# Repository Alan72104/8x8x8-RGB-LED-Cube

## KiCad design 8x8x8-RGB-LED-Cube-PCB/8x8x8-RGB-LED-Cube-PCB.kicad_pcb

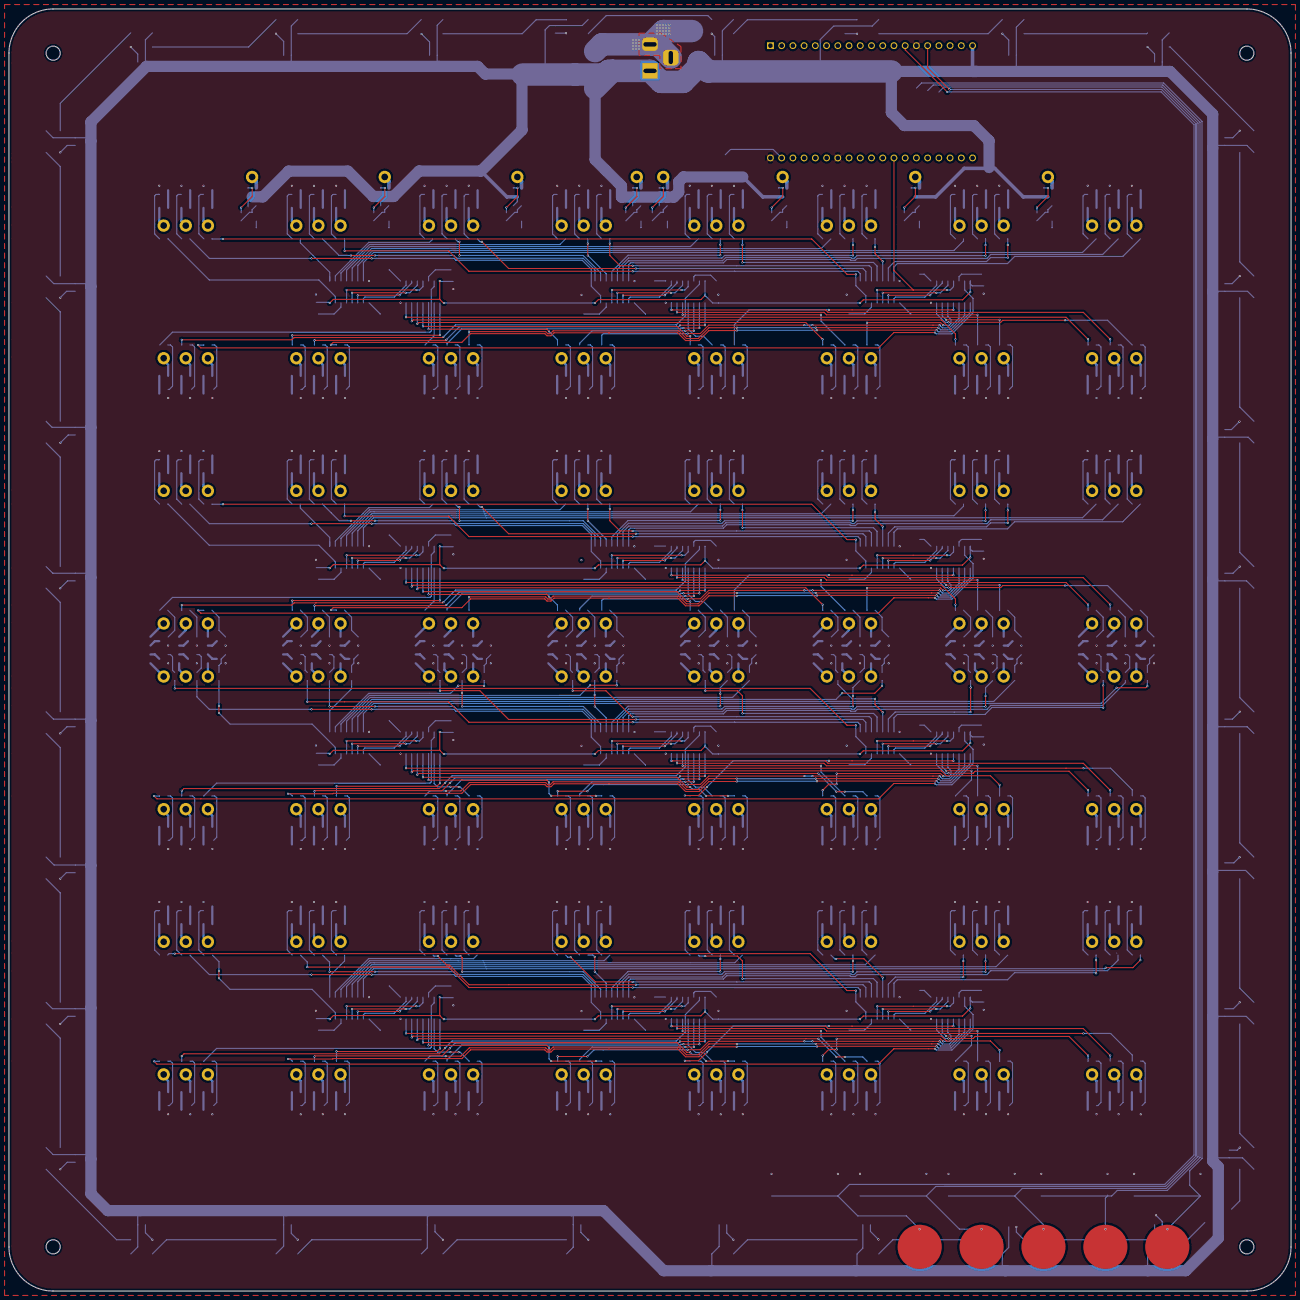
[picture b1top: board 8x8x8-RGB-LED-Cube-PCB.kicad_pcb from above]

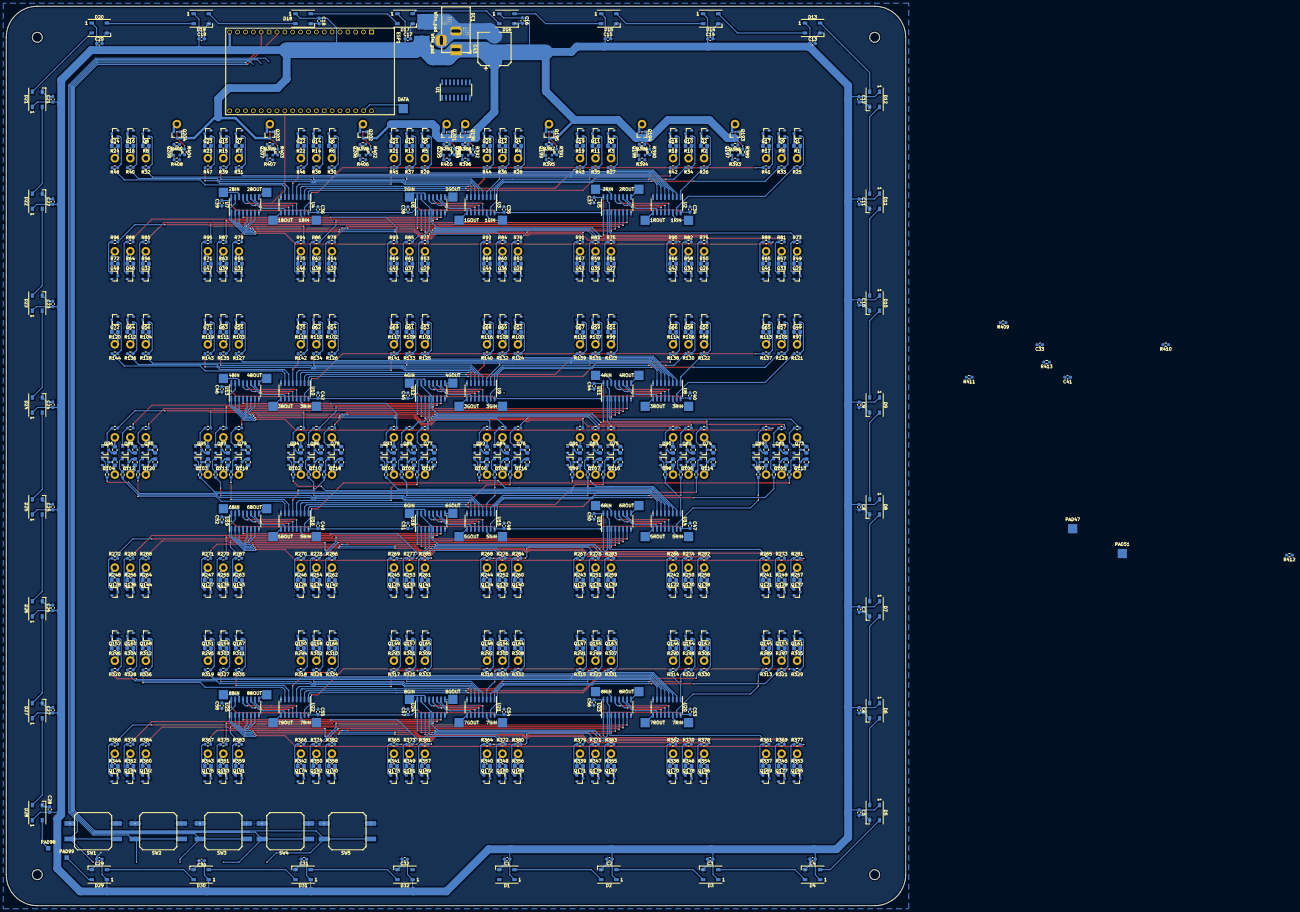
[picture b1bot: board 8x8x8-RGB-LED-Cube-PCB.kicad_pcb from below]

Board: 2 copper layers, 290.0 x 290.0 mm, 1007 parts (798 on the bottom side), 712 nets.

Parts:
C1, C2, C3, C4, C5, C6, C7, C8, C9, C10, C11, C12, C13, C14, C15, C16, C17, C18, C19, C20, C21, C22, C23, C24, C25, C26, C27, C28, C29, C30, C31, C32, C33, C34, C35, C36, C37, C38, C39, C40, C41, C42, C44, C45, C46, C47, C48, C49, C50, C51, C52, C53, C54, C55, C56, C57, C58: 0.1u; C_0603_1608Metric_Pad1.08x0.95mm_HandSolder
C43: 1000uF; CP_Elec_10x10.5
D1, D2, D3, D4, D5, D6, D7, D8, D9, D10, D11, D12, D13, D14, D15, D16, D17, D18, D19, D20, D21, D22, D23, D24, D25, D26, D27, D28, D29, D30, D31, D32: WS2812B; LED_WS2812B_PLCC4_5.0x5.0mm_P3.2mm
DC1: Barrel_Jack_Switch; BarrelJack_Horizontal
ESP1: ESP32-DEVKITC-32D; MODULE_ESP32-DEVKITC-32D
H1, H2, H3, H4, H5, H6, H7, H8, H9, H10, H11, H12, H13, H14, H15, H16, H17, H18, H19, H20, H21, H22, H23, H24, H25, H26, H27, H28, H29, H30, H31, H32, H33, H34, H35, H36, H37, H38, H39, H40, H41, H42, H43, H44, H45, H46, H47, H48, H49, H50, H51, H52, H53, H54, H55, H56, H57, H58, H59, H60, H61, H62, H63, H64, H65, H66, H67, H68, H69, H70, H71, H72, H73, H74, H75, H76, H77, H78, H79, H80, H81, H82, H83, H84, H85, H86, H87, H88, H89, H90, H91, H92, H93, H94, H95, H96, H97, H98, H99, H100, H101, H102, H103, H104, H105, H106, H107, H108, H109, H110, H111, H112, H113, H114, H115, H116, H117, H118, H119, H120, H121, H122, H123, H124, H125, H126, H127, H128, H129, H130, H131, H132, H133, H134, H135, H136, H137, H138, H139, H140, H141, H142, H143, H144, H145, H146, H147, H148, H149, H150, H151, H152, H153, H154, H155, H156, H157, H158, H159, H160, H161, H162, H163, H164, H165, H166, H167, H168, H169, H170, H171, H172, H173, H174, H175, H176, H177, H178, H179, H180, H181, H182, H183, H184, H185, H186, H187, H188, H189, H190, H191, H192, H193, H194, H195, H196, H197, H198, H199, H200: Wire_hole_1.2_2.5; Wire_hole_1.5_2.8
H201, H202, H203, H204: MountingHole; MountingHole_3.2mm_M3
PAD1: DATA; Solder_pad_3x3mm
PAD2: 1ROUT; Solder_pad_3x3mm
PAD3: 1GOUT; Solder_pad_3x3mm
PAD4: 1BOUT; Solder_pad_3x3mm
PAD5: 1RIN; Solder_pad_3x3mm
PAD6: 1GIN; Solder_pad_3x3mm
PAD7: 1BIN; Solder_pad_3x3mm
PAD8: 2ROUT; Solder_pad_3x3mm
PAD9: 2GOUT; Solder_pad_3x3mm
PAD10: 2BOUT; Solder_pad_3x3mm
PAD11: 2RIN; Solder_pad_3x3mm
PAD12: 2GIN; Solder_pad_3x3mm
PAD13: 2BIN; Solder_pad_3x3mm
PAD14: 3ROUT; Solder_pad_3x3mm
PAD15: 3GOUT; Solder_pad_3x3mm
PAD16: 3BOUT; Solder_pad_3x3mm
PAD17: 3RIN; Solder_pad_3x3mm
PAD18: 3GIN; Solder_pad_3x3mm
PAD19: 3BIN; Solder_pad_3x3mm
PAD20: 4ROUT; Solder_pad_3x3mm
PAD21: 4GOUT; Solder_pad_3x3mm
PAD22: 4BOUT; Solder_pad_3x3mm
PAD23: 4RIN; Solder_pad_3x3mm
PAD24: 4GIN; Solder_pad_3x3mm
PAD25: 4BIN; Solder_pad_3x3mm
PAD26: 5ROUT; Solder_pad_3x3mm
PAD27: 5GOUT; Solder_pad_3x3mm
PAD28: 5BOUT; Solder_pad_3x3mm
PAD29: 5RIN; Solder_pad_3x3mm
PAD30: 5GIN; Solder_pad_3x3mm
PAD31: 5BIN; Solder_pad_3x3mm
PAD32: 6ROUT; Solder_pad_3x3mm
PAD33: 6GOUT; Solder_pad_3x3mm
PAD34: 6BOUT; Solder_pad_3x3mm
PAD35: 6RIN; Solder_pad_3x3mm
PAD36: 6GIN; Solder_pad_3x3mm
PAD37: 6BIN; Solder_pad_3x3mm
PAD38: 7ROUT; Solder_pad_3x3mm
PAD39: 7GOUT; Solder_pad_3x3mm
PAD40: 7BOUT; Solder_pad_3x3mm
PAD41: 7RIN; Solder_pad_3x3mm
PAD42: 7GIN; Solder_pad_3x3mm
PAD43: 7BIN; Solder_pad_3x3mm
PAD44: 8ROUT; Solder_pad_3x3mm
PAD45: 8GOUT; Solder_pad_3x3mm
PAD46: 8BOUT; Solder_pad_3x3mm
PAD47: LAYEROUT; Solder_pad_3x3mm
PAD48: 8RIN; Solder_pad_3x3mm
PAD49: 8GIN; Solder_pad_3x3mm
PAD50: 8BIN; Solder_pad_3x3mm
PAD51: LAYERIN; Solder_pad_3x3mm
PAD52, PAD53: Wire_pad; Solder_pad_5x5mm
PAD98, PAD99: Wire_pad; Solder_pad_1.5x1.5mm
Q1, Q2, Q3, Q4, Q5, Q6, Q7, Q8, Q9, Q10, Q11, Q12, Q13, Q14, Q15, Q16, Q17, Q18, Q19, Q20, Q21, Q22, Q23, Q24, Q25, Q26, Q27, Q28, Q29, Q30, Q31, Q32, Q33, Q34, Q35, Q36, Q37, Q38, Q39, Q40, Q41, Q42, Q43, Q44, Q45, Q46, Q47, Q48, Q49, Q50, Q51, Q52, Q53, Q54, Q55, Q56, Q57, Q58, Q59, Q60, Q61, Q62, Q63, Q64, Q65, Q66, Q67, Q68, Q69, Q70, Q71, Q72, Q73, Q74, Q75, Q76, Q77, Q78, Q79, Q80, Q81, Q82, Q83, Q84, Q85, Q86, Q87, Q88, Q89, Q90, Q91, Q92, Q93, Q94, Q95, Q96, Q97, Q98, Q99, Q100, Q101, Q102, Q103, Q104, Q105, Q106, Q107, Q108, Q109, Q110, Q111, Q112, Q113, Q114, Q115, Q116, Q117, Q118, Q119, Q120, Q121, Q122, Q123, Q124, Q125, Q126, Q127, Q128, Q129, Q130, Q131, Q132, Q133, Q134, Q135, Q136, Q137, Q138, Q139, Q140, Q141, Q142, Q143, Q144, Q145, Q146, Q147, Q148, Q149, Q150, Q151, Q152, Q153, Q154, Q155, Q156, Q157, Q158, Q159, Q160, Q161, Q162, Q163, Q164, Q165, Q166, Q167, Q168, Q169, Q170, Q171, Q172, Q173, Q174, Q175, Q176, Q177, Q178, Q179, Q180, Q181, Q182, Q183, Q184, Q185, Q186, Q187, Q188, Q189, Q190, Q191, Q192, Q197, Q198, Q199, Q200, Q205, Q206, Q207, Q208: MMBT5551; SOT-23
Q193, Q194, Q195, Q196, Q201, Q202, Q203, Q204: IRLML6401; SOT-23
R1, R2, R3, R4, R5, R6, R7, R8, R49, R50, R51, R52, R53, R54, R55, R56, R97, R98, R99, R100, R101, R102, R103, R104, R145, R146, R147, R148, R149, R150, R151, R152, R193, R194, R195, R196, R197, R198, R199, R200, R241, R242, R243, R244, R245, R246, R247, R248, R289, R290, R291, R292, R293, R294, R295, R296, R337, R338, R339, R340, R341, R342, R343, R344: 330; R_0805_2012Metric_Pad1.20x1.40mm_HandSolder
R9, R10, R11, R12, R13, R14, R15, R16, R17, R18, R19, R20, R21, R22, R23, R24, R57, R58, R59, R60, R61, R62, R63, R64, R65, R66, R67, R68, R69, R70, R71, R72, R105, R106, R107, R108, R109, R110, R111, R112, R113, R114, R115, R116, R117, R118, R119, R120, R153, R154, R155, R156, R157, R158, R159, R160, R161, R162, R163, R164, R165, R166, R167, R168, R201, R202, R203, R204, R205, R206, R207, R208, R209, R210, R211, R212, R213, R214, R215, R216, R249, R250, R251, R252, R253, R254, R255, R256, R257, R258, R259, R260, R261, R262, R263, R264, R297, R298, R299, R300, R301, R302, R303, R304, R305, R306, R307, R308, R309, R310, R311, R312, R345, R346, R347, R348, R349, R350, R351, R352, R353, R354, R355, R356, R357, R358, R359, R360: 665; R_0805_2012Metric_Pad1.20x1.40mm_HandSolder
R25, R26, R27, R28, R29, R30, R31, R32, R33, R34, R35, R36, R37, R38, R39, R40, R41, R42, R43, R44, R45, R46, R47, R48, R73, R74, R75, R76, R77, R78, R79, R80, R81, R82, R83, R84, R85, R86, R87, R88, R89, R90, R91, R92, R93, R94, R95, R96, R121, R122, R123, R124, R125, R126, R127, R128, R129, R130, R131, R132, R133, R134, R135, R136, R137, R138, R139, R140, R141, R142, R143, R144, R169, R170, R171, R172, R173, R174, R175, R176, R177, R178, R179, R180, R181, R182, R183, R184, R185, R186, R187, R188, R189, R190, R191, R192, R217, R218, R219, R220, R221, R222, R223, R224, R225, R226, R227, R228, R229, R230, R231, R232, R233, R234, R235, R236, R237, R238, R239, R240, R265, R266, R267, R268, R269, R270, R271, R272, R273, R274, R275, R276, R277, R278, R279, R280, R281, R282, R283, R284, R285, R286, R287, R288, R313, R314, R315, R316, R317, R318, R319, R320, R321, R322, R323, R324, R325, R326, R327, R328, R329, R330, R331, R332, R333, R334, R335, R336, R361, R362, R363, R364, R365, R366, R367, R368, R369, R370, R371, R372, R373, R374, R375, R376, R377, R378, R379, R380, R381, R382, R383, R384, R385, R386, R387, R388, R393, R394, R395, R396, R397, R398, R399, R400, R405, R406, R407, R408, R409, R410, R411, R412, R413: 10k; R_0603_1608Metric_Pad0.98x0.95mm_HandSolder
R389, R390, R391, R392, R401, R402, R403, R404: 100; R_0603_1608Metric_Pad0.98x0.95mm_HandSolder
SW1, SW2, SW3, SW4, SW5: SW_MEC_5E; SW_TACTILE_12x12mm
TOUCH1, TOUCH2, TOUCH3, TOUCH4, TOUCH5: Touch_pad
U1, U2, U3, U4, U5, U6, U7, U8, U9, U10, U11, U12, U13, U14, U15, U16, U17, U18, U19, U20, U21, U22, U23, U24, U25: 74HC595; SOIC-16_3.9x9.9mm_P1.27mm

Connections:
+3V3: ESP1.1, R413.2
+5V: C1.1, C2.1, C3.1, C4.1, C5.1, C6.1, C7.1, C8.1, C9.1, C10.1, C11.1, C12.1, C13.1, C14.1, C15.1, C16.1, C17.1, C18.1, C19.1, C20.1, C21.1, C22.1, C23.1, C24.1, C25.1, C26.1, C27.1, C28.1, C29.1, C30.1, C31.1, C32.1, C33.1, C34.1, C35.1, C36.1, C37.1, C38.1, C39.1, C40.1, C41.1, C42.1, C43.1, C44.1, C45.1, C46.1, C47.1, C48.1, C49.1, C50.1, C51.1, C52.1, C53.1, C54.1, C55.1, C56.1, C57.1, C58.1, D1.1, D2.1, D3.1, D4.1, D5.1, D6.1, D7.1, D8.1, D9.1, D10.1, D11.1, D12.1, D13.1, D14.1, D15.1, D16.1, D17.1, D18.1, D19.1, D20.1, D21.1, D22.1, D23.1, D24.1, D25.1, D26.1, D27.1, D28.1, D29.1, D30.1, D31.1, D32.1, DC1.1, ESP1.19, PAD52.1, Q193.3, Q194.3, Q195.3, Q196.3, Q201.3, Q202.3, Q203.3, Q204.3, R385.1, R386.1, R387.1, R388.1, R397.1, R398.1, R399.1, R400.1, U1.16, U2.16, U3.16, U4.16, U5.16, U6.16, U7.16, U8.16, U9.16, U10.16, U11.16, U12.16, U13.16, U14.16, U15.16, U16.16, U17.16, U18.16, U19.16, U20.16, U21.16, U22.16, U23.16, U24.16, U25.16
B1-1: R41.2, U4.15
B1-2: R42.2, U4.1
B1-3: R43.2, U4.2
B1-4: R44.2, U4.3
B1-5: R45.2, U4.4
B1-6: R46.2, U4.5
B1-7: R47.2, U4.6
B1-8: R48.2, U4.7
B2-1: R89.2, U7.15
B2-2: R90.2, U7.1
B2-3: R91.2, U7.2
B2-4: R92.2, U7.3
B2-5: R93.2, U7.4
B2-6: R94.2, U7.5
B2-7: R95.2, U7.6
B2-8: R96.2, U7.7
B3-1: R137.2, U10.15
B3-2: R138.2, U10.1
B3-3: R139.2, U10.2
B3-4: R140.2, U10.3
B3-5: R141.2, U10.4
B3-6: R142.2, U10.5
B3-7: R143.2, U10.6
B3-8: R144.2, U10.7
B4-1: R185.2, U13.15
B4-2: R186.2, U13.1
B4-3: R187.2, U13.2
B4-4: R188.2, U13.3
B4-5: R189.2, U13.4
B4-6: R190.2, U13.5
B4-7: R191.2, U13.6
B4-8: R192.2, U13.7
B5-1: R233.2, U16.15
B5-2: R234.2, U16.1
B5-3: R235.2, U16.2
B5-4: R236.2, U16.3
B5-5: R237.2, U16.4
B5-6: R238.2, U16.5
B5-7: R239.2, U16.6
B5-8: R240.2, U16.7
B6-1: R281.2, U19.15
B6-2: R282.2, U19.1
B6-3: R283.2, U19.2
B6-4: R284.2, U19.3
B6-5: R285.2, U19.4
B6-6: R286.2, U19.5
B6-7: R287.2, U19.6
B6-8: R288.2, U19.7
B7-1: R329.2, U22.15
B7-2: R330.2, U22.1
B7-3: R331.2, U22.2
B7-4: R332.2, U22.3
B7-5: R333.2, U22.4
B7-6: R334.2, U22.5
B7-7: R335.2, U22.6
B7-8: R336.2, U22.7
B8-1: R377.2, U25.15
B8-2: R378.2, U25.1
B8-3: R379.2, U25.2
B8-4: R380.2, U25.3
B8-5: R381.2, U25.4
B8-6: R382.2, U25.5
B8-7: R383.2, U25.6
B8-8: R384.2, U25.7
G1-1: R33.2, U3.15
G1-2: R34.2, U3.1
G1-3: R35.2, U3.2
G1-4: R36.2, U3.3
G1-5: R37.2, U3.4
G1-6: R38.2, U3.5
G1-7: R39.2, U3.6
G1-8: R40.2, U3.7
G2-1: R81.2, U6.15
G2-2: R82.2, U6.1
G2-3: R83.2, U6.2
G2-4: R84.2, U6.3
G2-5: R85.2, U6.4
G2-6: R86.2, U6.5
G2-7: R87.2, U6.6
G2-8: R88.2, U6.7
G3-1: R129.2, U9.15
G3-2: R130.2, U9.1
G3-3: R131.2, U9.2
G3-4: R132.2, U9.3
G3-5: R133.2, U9.4
G3-6: R134.2, U9.5
G3-7: R135.2, U9.6
G3-8: R136.2, U9.7
G4-1: R177.2, U12.15
G4-2: R178.2, U12.1
G4-3: R179.2, U12.2
G4-4: R180.2, U12.3
G4-5: R181.2, U12.4
G4-6: R182.2, U12.5
G4-7: R183.2, U12.6
G4-8: R184.2, U12.7
G5-1: R225.2, U15.15
G5-2: R226.2, U15.1
G5-3: R227.2, U15.2
G5-4: R228.2, U15.3
G5-5: R229.2, U15.4
G5-6: R230.2, U15.5
G5-7: R231.2, U15.6
G5-8: R232.2, U15.7
G6-1: R273.2, U18.15
G6-2: R274.2, U18.1
G6-3: R275.2, U18.2
G6-4: R276.2, U18.3
G6-5: R277.2, U18.4
G6-6: R278.2, U18.5
G6-7: R279.2, U18.6
G6-8: R280.2, U18.7
G7-1: R321.2, U21.15
G7-2: R322.2, U21.1
G7-3: R323.2, U21.2
G7-4: R324.2, U21.3
G7-5: R325.2, U21.4
G7-6: R326.2, U21.5
G7-7: R327.2, U21.6
G7-8: R328.2, U21.7
G8-1: R369.2, U24.15
G8-2: R370.2, U24.1
G8-3: R371.2, U24.2
G8-4: R372.2, U24.3
G8-5: R373.2, U24.4
G8-6: R374.2, U24.5
G8-7: R375.2, U24.6
G8-8: R376.2, U24.7
GND: C1.2, C2.2, C3.2, C4.2, C5.2, C6.2, C7.2, C8.2, C9.2, C10.2, C11.2, C12.2, C13.2, C14.2, C15.2, C16.2, C17.2, C18.2, C19.2, C20.2, C21.2, C22.2, C23.2, C24.2, C25.2, C26.2, C27.2, C28.2, C29.2, C30.2, C31.2, C32.2, C33.2, C34.2, C35.2, C36.2, C37.2, C38.2, C39.2, C40.2, C41.2, C42.2, C43.2, C44.2, C45.2, C46.2, C47.2, C48.2, C49.2, C50.2, C51.2, C52.2, C53.2, C54.2, C55.2, C56.2, C57.2, C58.2, D1.3, D2.3, D3.3, D4.3, D5.3, D6.3, D7.3, D8.3, D9.3, D10.3, D11.3, D12.3, D13.3, D14.3, D15.3, D16.3, D17.3, D18.3, D19.3, D20.3, D21.3, D22.3, D23.3, D24.3, D25.3, D26.3, D27.3, D28.3, D29.3, D30.3, D31.3, D32.3, DC1.2, DC1.3, ESP1.14, ESP1.20, ESP1.26, PAD53.1, Q1.2, Q2.2, Q3.2, Q4.2, Q5.2, Q6.2, Q7.2, Q8.2, Q9.2, Q10.2, Q11.2, Q12.2, Q13.2, Q14.2, Q15.2, Q16.2, Q17.2, Q18.2, Q19.2, Q20.2, Q21.2, Q22.2, Q23.2, Q24.2, Q25.2, Q26.2, Q27.2, Q28.2, Q29.2, Q30.2, Q31.2, Q32.2, Q33.2, Q34.2, Q35.2, Q36.2, Q37.2, Q38.2, Q39.2, Q40.2, Q41.2, Q42.2, Q43.2, Q44.2, Q45.2, Q46.2, Q47.2, Q48.2, Q49.2, Q50.2, Q51.2, Q52.2, Q53.2, Q54.2, Q55.2, Q56.2, Q57.2, Q58.2, Q59.2, Q60.2, Q61.2, Q62.2, Q63.2, Q64.2, Q65.2, Q66.2, Q67.2, Q68.2, Q69.2, Q70.2, Q71.2, Q72.2, Q73.2, Q74.2, Q75.2, Q76.2, Q77.2, Q78.2, Q79.2, Q80.2, Q81.2, Q82.2, Q83.2, Q84.2, Q85.2, Q86.2, Q87.2, Q88.2, Q89.2, Q90.2, Q91.2, Q92.2, Q93.2, Q94.2, Q95.2, Q96.2, Q97.2, Q98.2, Q99.2, Q100.2, Q101.2, Q102.2, Q103.2, Q104.2, Q105.2, Q106.2, Q107.2, Q108.2, Q109.2, Q110.2, Q111.2, Q112.2, Q113.2, Q114.2, Q115.2, Q116.2, Q117.2, Q118.2, Q119.2, Q120.2, Q121.2, Q122.2, Q123.2, Q124.2, Q125.2, Q126.2, Q127.2, Q128.2, Q129.2, Q130.2, Q131.2, Q132.2, Q133.2, Q134.2, Q135.2, Q136.2, Q137.2, Q138.2, Q139.2, Q140.2, Q141.2, Q142.2, Q143.2, Q144.2, Q145.2, Q146.2, Q147.2, Q148.2, Q149.2, Q150.2, Q151.2, Q152.2, Q153.2, Q154.2, Q155.2, Q156.2, Q157.2, Q158.2, Q159.2, Q160.2, Q161.2, Q162.2, Q163.2, Q164.2, Q165.2, Q166.2, Q167.2, Q168.2, Q169.2, Q170.2, Q171.2, Q172.2, Q173.2, Q174.2, Q175.2, Q176.2, Q177.2, Q178.2, Q179.2, Q180.2, Q181.2, Q182.2, Q183.2, Q184.2, Q185.2, Q186.2, Q187.2, Q188.2, Q189.2, Q190.2, Q191.2, Q192.2, Q197.2, Q198.2, Q199.2, Q200.2, Q205.2, Q206.2, Q207.2, Q208.2, R409.2, R410.1, R411.1, R412.1, SW1.3, SW1.4, SW2.3, SW2.4, SW3.3, SW3.4, SW4.3, SW4.4, SW5.3, SW5.4, U1.8, U2.8, U3.8, U4.8, U5.8, U6.8, U7.8, U8.8, U9.8, U10.8, U11.8, U12.8, U13.8, U14.8, U15.8, U16.8, U17.8, U18.8, U19.8, U20.8, U21.8, U22.8, U23.8, U24.8, U25.8
LED_strip: D1.4, ESP1.12
Layer1: R393.1, U1.15
Layer2: R394.1, U1.1
Layer3: R395.1, U1.2
Layer4: R396.1, U1.3
Layer5: R405.1, U1.4
Layer6: R406.1, U1.5
Layer7: R407.1, U1.6
Layer8: R408.1, U1.7
unnamed: D1.2, D2.4
unnamed: D2.2, D3.4
unnamed: D3.2, D4.4
unnamed: D4.2, D5.4
unnamed: D5.2, D6.4
unnamed: D6.2, D7.4
unnamed: D7.2, D8.4
unnamed: D8.2, D9.4
unnamed: D10.2, D11.4
unnamed: D9.2, D10.4
unnamed: D11.2, D12.4
unnamed: D12.2, D13.4
unnamed: D13.2, D14.4
unnamed: D14.2, D15.4
unnamed: D15.2, D16.4
unnamed: D16.2, D17.4
unnamed: D17.2, D18.4
unnamed: D18.2, D19.4
unnamed: D19.2, D20.4
unnamed: D20.2, D21.4
unnamed: D21.2, D22.4
unnamed: D22.2, D23.4
unnamed: D23.2, D24.4
unnamed: D24.2, D25.4
unnamed: D25.2, D26.4
unnamed: D26.2, D27.4
unnamed: D27.2, D28.4
unnamed: D28.2, PAD98.1
unnamed: D29.2, D30.4
unnamed: D29.4, PAD99.1
unnamed: D30.2, D31.4
unnamed: D31.2, D32.4
unnamed: ESP1.21, PAD1.1, R409.1
unnamed: H193.1, Q193.2
unnamed: H194.1, Q194.2
unnamed: H195.1, Q195.2
unnamed: H196.1, Q196.2
unnamed: H197.1, Q201.2
unnamed: H198.1, Q202.2
unnamed: H199.1, Q203.2
unnamed: H200.1, Q204.2
unnamed: PAD2.1, U2.9
unnamed: PAD3.1, U3.9
unnamed: PAD4.1, U4.9
unnamed: PAD5.1, U2.14
unnamed: PAD6.1, U3.14
unnamed: PAD7.1, U4.14
unnamed: PAD8.1, U5.9
unnamed: PAD9.1, U6.9
unnamed: PAD10.1, U7.9
unnamed: PAD11.1, U5.14
unnamed: PAD12.1, U6.14
unnamed: PAD13.1, U7.14
unnamed: PAD14.1, U8.9
unnamed: PAD15.1, U9.9
unnamed: PAD16.1, U10.9
unnamed: PAD17.1, U8.14
unnamed: PAD18.1, U9.14
unnamed: PAD19.1, U10.14
unnamed: PAD20.1, U11.9
unnamed: PAD21.1, U12.9
unnamed: PAD22.1, U13.9
unnamed: PAD23.1, U11.14
unnamed: PAD24.1, U12.14
unnamed: PAD25.1, U13.14
unnamed: PAD26.1, U14.9
unnamed: PAD27.1, U15.9
unnamed: PAD28.1, U16.9
unnamed: PAD29.1, U14.14
unnamed: PAD30.1, U15.14
unnamed: PAD31.1, U16.14
unnamed: PAD32.1, U17.9
unnamed: PAD33.1, U18.9
unnamed: PAD34.1, U19.9
unnamed: PAD35.1, U17.14
unnamed: PAD36.1, U18.14
unnamed: PAD37.1, U19.14
unnamed: PAD38.1, U20.9
unnamed: PAD39.1, U21.9
unnamed: PAD40.1, U22.9
unnamed: PAD41.1, U20.14
unnamed: PAD42.1, U21.14
unnamed: PAD43.1, U22.14
unnamed: PAD44.1, U23.9
unnamed: PAD45.1, U24.9
unnamed: PAD46.1, U25.9
unnamed: PAD47.1, U1.9
unnamed: PAD48.1, U23.14
unnamed: PAD49.1, U24.14
unnamed: PAD50.1, U25.14
unnamed: PAD51.1, U1.14
unnamed: Q1.1, R25.1
unnamed: Q1.3, R1.2
unnamed: Q2.1, R26.1
unnamed: Q2.3, R2.2
unnamed: Q3.1, R27.1
unnamed: Q3.3, R3.2
unnamed: Q4.1, R28.1
unnamed: Q4.3, R4.2
unnamed: Q5.1, R29.1
unnamed: Q5.3, R5.2
unnamed: Q6.1, R30.1
unnamed: Q6.3, R6.2
unnamed: Q7.1, R31.1
unnamed: Q7.3, R7.2
unnamed: Q8.1, R32.1
unnamed: Q8.3, R8.2
unnamed: Q9.1, R33.1
unnamed: Q9.3, R9.2
unnamed: Q10.1, R34.1
unnamed: Q10.3, R10.2
unnamed: Q11.1, R35.1
unnamed: Q11.3, R11.2
unnamed: Q12.1, R36.1
unnamed: Q12.3, R12.2
unnamed: Q13.1, R37.1
unnamed: Q13.3, R13.2
unnamed: Q14.1, R38.1
unnamed: Q14.3, R14.2
unnamed: Q15.1, R39.1
unnamed: Q15.3, R15.2
unnamed: Q16.1, R40.1
unnamed: Q16.3, R16.2
unnamed: Q17.1, R41.1
unnamed: Q17.3, R17.2
unnamed: Q18.1, R42.1
unnamed: Q18.3, R18.2
unnamed: Q19.1, R43.1
unnamed: Q19.3, R19.2
unnamed: Q20.1, R44.1
unnamed: Q20.3, R20.2
unnamed: Q21.1, R45.1
unnamed: Q21.3, R21.2
unnamed: Q22.1, R46.1
unnamed: Q22.3, R22.2
unnamed: Q23.1, R47.1
unnamed: Q23.3, R23.2
unnamed: Q24.1, R48.1
unnamed: Q24.3, R24.2
unnamed: Q25.1, R73.1
unnamed: Q25.3, R49.2
unnamed: Q26.1, R74.1
unnamed: Q26.3, R50.2
unnamed: Q27.1, R75.1
unnamed: Q27.3, R51.2
unnamed: Q28.1, R76.1
unnamed: Q28.3, R52.2
unnamed: Q29.1, R77.1
unnamed: Q29.3, R53.2
unnamed: Q30.1, R78.1
unnamed: Q30.3, R54.2
unnamed: Q31.1, R79.1
unnamed: Q31.3, R55.2
unnamed: Q32.1, R80.1
unnamed: Q32.3, R56.2
unnamed: Q33.1, R81.1
unnamed: Q33.3, R57.2
unnamed: Q34.1, R82.1
unnamed: Q34.3, R58.2
unnamed: Q35.1, R83.1
unnamed: Q35.3, R59.2
unnamed: Q36.1, R84.1
unnamed: Q36.3, R60.2
unnamed: Q37.1, R85.1
unnamed: Q37.3, R61.2
unnamed: Q38.1, R86.1
unnamed: Q38.3, R62.2
unnamed: Q39.1, R87.1
unnamed: Q39.3, R63.2
unnamed: Q40.1, R88.1
unnamed: Q40.3, R64.2
unnamed: Q41.1, R89.1
unnamed: Q41.3, R65.2
unnamed: Q42.1, R90.1
unnamed: Q42.3, R66.2
unnamed: Q43.1, R91.1
unnamed: Q43.3, R67.2
unnamed: Q44.1, R92.1
unnamed: Q44.3, R68.2
unnamed: Q45.1, R93.1
unnamed: Q45.3, R69.2
unnamed: Q46.1, R94.1
unnamed: Q46.3, R70.2
unnamed: Q47.1, R95.1
unnamed: Q47.3, R71.2
unnamed: Q48.1, R96.1
unnamed: Q48.3, R72.2
unnamed: Q49.1, R121.1
unnamed: Q49.3, R97.2
unnamed: Q50.1, R122.1
unnamed: Q50.3, R98.2
unnamed: Q51.1, R123.1
unnamed: Q51.3, R99.2
unnamed: Q52.1, R124.1
unnamed: Q52.3, R100.2
unnamed: Q53.1, R125.1
unnamed: Q53.3, R101.2
unnamed: Q54.1, R126.1
unnamed: Q54.3, R102.2
unnamed: Q55.1, R127.1
unnamed: Q55.3, R103.2
unnamed: Q56.1, R128.1
unnamed: Q56.3, R104.2
unnamed: Q57.1, R129.1
unnamed: Q57.3, R105.2
unnamed: Q58.1, R130.1
unnamed: Q58.3, R106.2
unnamed: Q59.1, R131.1
unnamed: Q59.3, R107.2
unnamed: Q60.1, R132.1
unnamed: Q60.3, R108.2
unnamed: Q61.1, R133.1
unnamed: Q61.3, R109.2
unnamed: Q62.1, R134.1
unnamed: Q62.3, R110.2
unnamed: Q63.1, R135.1
unnamed: Q63.3, R111.2
unnamed: Q64.1, R136.1
unnamed: Q64.3, R112.2
unnamed: Q65.1, R137.1
unnamed: Q65.3, R113.2
unnamed: Q66.1, R138.1
unnamed: Q66.3, R114.2
unnamed: Q67.1, R139.1
unnamed: Q67.3, R115.2
unnamed: Q68.1, R140.1
unnamed: Q68.3, R116.2
unnamed: Q69.1, R141.1
unnamed: Q69.3, R117.2
unnamed: Q70.1, R142.1
unnamed: Q70.3, R118.2
unnamed: Q71.1, R143.1
unnamed: Q71.3, R119.2
unnamed: Q72.1, R144.1
unnamed: Q72.3, R120.2
unnamed: Q73.1, R169.1
unnamed: Q73.3, R145.2
unnamed: Q74.1, R170.1
unnamed: Q74.3, R146.2
unnamed: Q75.1, R171.1
unnamed: Q75.3, R147.2
unnamed: Q76.1, R172.1
unnamed: Q76.3, R148.2
unnamed: Q77.1, R173.1
unnamed: Q77.3, R149.2
unnamed: Q78.1, R174.1
unnamed: Q78.3, R150.2
unnamed: Q79.1, R175.1
unnamed: Q79.3, R151.2
unnamed: Q80.1, R176.1
unnamed: Q80.3, R152.2
unnamed: Q81.1, R177.1
unnamed: Q81.3, R153.2
unnamed: Q82.1, R178.1
unnamed: Q82.3, R154.2
unnamed: Q83.1, R179.1
unnamed: Q83.3, R155.2
unnamed: Q84.1, R180.1
unnamed: Q84.3, R156.2
unnamed: Q85.1, R181.1
unnamed: Q85.3, R157.2
unnamed: Q86.1, R182.1
unnamed: Q86.3, R158.2
unnamed: Q87.1, R183.1
unnamed: Q87.3, R159.2
unnamed: Q88.1, R184.1
unnamed: Q88.3, R160.2
unnamed: Q89.1, R185.1
unnamed: Q89.3, R161.2
unnamed: Q90.1, R186.1
unnamed: Q90.3, R162.2
unnamed: Q91.1, R187.1
unnamed: Q91.3, R163.2
unnamed: Q92.1, R188.1
unnamed: Q92.3, R164.2
unnamed: Q93.1, R189.1
unnamed: Q93.3, R165.2
unnamed: Q94.1, R190.1
unnamed: Q94.3, R166.2
unnamed: Q95.1, R191.1
unnamed: Q95.3, R167.2
unnamed: Q96.1, R192.1
unnamed: Q96.3, R168.2
unnamed: Q97.1, R217.1
unnamed: Q97.3, R193.2
unnamed: Q98.1, R218.1
unnamed: Q98.3, R194.2
unnamed: Q99.1, R219.1
unnamed: Q99.3, R195.2
unnamed: Q100.1, R220.1
unnamed: Q100.3, R196.2
unnamed: Q101.1, R221.1
unnamed: Q101.3, R197.2
unnamed: Q102.1, R222.1
unnamed: Q102.3, R198.2
unnamed: Q103.1, R223.1
unnamed: Q103.3, R199.2
unnamed: Q104.1, R224.1
unnamed: Q104.3, R200.2
unnamed: Q105.1, R225.1
unnamed: Q105.3, R201.2
unnamed: Q106.1, R226.1
unnamed: Q106.3, R202.2
unnamed: Q107.1, R227.1
unnamed: Q107.3, R203.2
unnamed: Q108.1, R228.1
unnamed: Q108.3, R204.2
unnamed: Q109.1, R229.1
unnamed: Q109.3, R205.2
unnamed: Q110.1, R230.1
unnamed: Q110.3, R206.2
unnamed: Q111.1, R231.1
unnamed: Q111.3, R207.2
unnamed: Q112.1, R232.1
unnamed: Q112.3, R208.2
unnamed: Q113.1, R233.1
unnamed: Q113.3, R209.2
unnamed: Q114.1, R234.1
unnamed: Q114.3, R210.2
unnamed: Q115.1, R235.1
unnamed: Q115.3, R211.2
unnamed: Q116.1, R236.1
unnamed: Q116.3, R212.2
unnamed: Q117.1, R237.1
unnamed: Q117.3, R213.2
unnamed: Q118.1, R238.1
unnamed: Q118.3, R214.2
unnamed: Q119.1, R239.1
unnamed: Q119.3, R215.2
unnamed: Q120.1, R240.1
unnamed: Q120.3, R216.2
unnamed: Q121.1, R265.1
unnamed: Q121.3, R241.2
unnamed: Q122.1, R266.1
unnamed: Q122.3, R242.2
unnamed: Q123.1, R267.1
unnamed: Q123.3, R243.2
unnamed: Q124.1, R268.1
unnamed: Q124.3, R244.2
unnamed: Q125.1, R269.1
unnamed: Q125.3, R245.2
unnamed: Q126.1, R270.1
unnamed: Q126.3, R246.2
unnamed: Q127.1, R271.1
unnamed: Q127.3, R247.2
unnamed: Q128.1, R272.1
unnamed: Q128.3, R248.2
unnamed: Q129.1, R273.1
unnamed: Q129.3, R249.2
unnamed: Q130.1, R274.1
unnamed: Q130.3, R250.2
unnamed: Q131.1, R275.1
unnamed: Q131.3, R251.2
unnamed: Q132.1, R276.1
unnamed: Q132.3, R252.2
unnamed: Q133.1, R277.1
unnamed: Q133.3, R253.2
unnamed: Q134.1, R278.1
unnamed: Q134.3, R254.2
unnamed: Q135.1, R279.1
unnamed: Q135.3, R255.2
unnamed: Q136.1, R280.1
unnamed: Q136.3, R256.2
unnamed: Q137.1, R281.1
unnamed: Q137.3, R257.2
unnamed: Q138.1, R282.1
unnamed: Q138.3, R258.2
unnamed: Q139.1, R283.1
unnamed: Q139.3, R259.2
unnamed: Q140.1, R284.1
unnamed: Q140.3, R260.2
unnamed: Q141.1, R285.1
unnamed: Q141.3, R261.2
unnamed: Q142.1, R286.1
unnamed: Q142.3, R262.2
unnamed: Q143.1, R287.1
unnamed: Q143.3, R263.2
unnamed: Q144.1, R288.1
unnamed: Q144.3, R264.2
unnamed: Q145.1, R313.1
unnamed: Q145.3, R289.2
unnamed: Q146.1, R314.1
unnamed: Q146.3, R290.2
unnamed: Q147.1, R315.1
unnamed: Q147.3, R291.2
unnamed: Q148.1, R316.1
unnamed: Q148.3, R292.2
unnamed: Q149.1, R317.1
unnamed: Q149.3, R293.2
unnamed: Q150.1, R318.1
unnamed: Q150.3, R294.2
unnamed: Q151.1, R319.1
unnamed: Q151.3, R295.2
unnamed: Q152.1, R320.1
unnamed: Q152.3, R296.2
unnamed: Q153.1, R321.1
unnamed: Q153.3, R297.2
unnamed: Q154.1, R322.1
unnamed: Q154.3, R298.2
unnamed: Q155.1, R323.1
unnamed: Q155.3, R299.2
unnamed: Q156.1, R324.1
unnamed: Q156.3, R300.2
unnamed: Q157.1, R325.1
unnamed: Q157.3, R301.2
unnamed: Q158.1, R326.1
unnamed: Q158.3, R302.2
unnamed: Q159.1, R327.1
unnamed: Q159.3, R303.2
unnamed: Q160.1, R328.1
unnamed: Q160.3, R304.2
unnamed: Q161.1, R329.1
unnamed: Q161.3, R305.2
unnamed: Q162.1, R330.1
unnamed: Q162.3, R306.2
unnamed: Q163.1, R331.1
unnamed: Q163.3, R307.2
unnamed: Q164.1, R332.1
unnamed: Q164.3, R308.2
unnamed: Q165.1, R333.1
unnamed: Q165.3, R309.2
unnamed: Q166.1, R334.1
unnamed: Q166.3, R310.2
unnamed: Q167.1, R335.1
unnamed: Q167.3, R311.2
unnamed: Q168.1, R336.1
unnamed: Q168.3, R312.2
unnamed: Q169.1, R361.1
unnamed: Q169.3, R337.2
unnamed: Q170.1, R362.1
unnamed: Q170.3, R338.2
unnamed: Q171.1, R363.1
unnamed: Q171.3, R339.2
unnamed: Q172.1, R364.1
unnamed: Q172.3, R340.2
unnamed: Q173.1, R365.1
unnamed: Q173.3, R341.2
unnamed: Q174.1, R366.1
unnamed: Q174.3, R342.2
unnamed: Q175.1, R367.1
unnamed: Q175.3, R343.2
unnamed: Q176.1, R368.1
unnamed: Q176.3, R344.2
unnamed: Q177.1, R369.1
unnamed: Q177.3, R345.2
unnamed: Q178.1, R370.1
unnamed: Q178.3, R346.2
unnamed: Q179.1, R371.1
unnamed: Q179.3, R347.2
unnamed: Q180.1, R372.1
unnamed: Q180.3, R348.2
unnamed: Q181.1, R373.1
unnamed: Q181.3, R349.2
unnamed: Q182.1, R374.1
unnamed: Q182.3, R350.2
unnamed: Q183.1, R375.1
unnamed: Q183.3, R351.2
unnamed: Q184.1, R376.1
unnamed: Q184.3, R352.2
unnamed: Q185.1, R377.1
unnamed: Q185.3, R353.2
unnamed: Q186.1, R378.1
unnamed: Q186.3, R354.2
unnamed: Q187.1, R379.1
unnamed: Q187.3, R355.2
unnamed: Q188.1, R380.1
unnamed: Q188.3, R356.2
unnamed: Q189.1, R381.1
unnamed: Q189.3, R357.2
unnamed: Q190.1, R382.1
unnamed: Q190.3, R358.2
unnamed: Q191.1, R383.1
unnamed: Q191.3, R359.2
unnamed: Q192.1, R384.1
unnamed: Q192.3, R360.2
unnamed: Q193.1, R389.1
unnamed: Q194.1, R390.1
unnamed: Q195.1, R391.1
unnamed: Q196.1, R392.1
unnamed: Q197.1, R393.2
unnamed: Q197.3, R385.2, R389.2
unnamed: Q198.1, R394.2
unnamed: Q198.3, R386.2, R390.2
unnamed: Q199.1, R395.2
unnamed: Q199.3, R387.2, R391.2
unnamed: Q200.1, R396.2
unnamed: Q200.3, R388.2, R392.2
unnamed: Q201.1, R401.1
unnamed: Q202.1, R402.1
unnamed: Q203.1, R403.1
unnamed: Q204.1, R404.1
unnamed: Q205.1, R405.2
unnamed: Q205.3, R397.2, R401.2
unnamed: Q206.1, R406.2
unnamed: Q206.3, R398.2, R402.2
unnamed: Q207.1, R407.2
unnamed: Q207.3, R399.2, R403.2
unnamed: Q208.1, R408.2
unnamed: Q208.3, R400.2, R404.2
R1-1: R25.2, U2.15
R1-2: R26.2, U2.1
R1-3: R27.2, U2.2
R1-4: R28.2, U2.3
R1-5: R29.2, U2.4
R1-6: R30.2, U2.5
R1-7: R31.2, U2.6
R1-8: R32.2, U2.7
R2-1: R73.2, U5.15
R2-2: R74.2, U5.1
R2-3: R75.2, U5.2
R2-4: R76.2, U5.3
R2-5: R77.2, U5.4
R2-6: R78.2, U5.5
R2-7: R79.2, U5.6
R2-8: R80.2, U5.7
R3-1: R121.2, U8.15
R3-2: R122.2, U8.1
R3-3: R123.2, U8.2
R3-4: R124.2, U8.3
R3-5: R125.2, U8.4
R3-6: R126.2, U8.5
R3-7: R127.2, U8.6
R3-8: R128.2, U8.7
R4-1: R169.2, U11.15
R4-2: R170.2, U11.1
R4-3: R171.2, U11.2
R4-4: R172.2, U11.3
R4-5: R173.2, U11.4
R4-6: R174.2, U11.5
R4-7: R175.2, U11.6
R4-8: R176.2, U11.7
R5-1: R217.2, U14.15
R5-2: R218.2, U14.1
R5-3: R219.2, U14.2
R5-4: R220.2, U14.3
R5-5: R221.2, U14.4
R5-6: R222.2, U14.5
R5-7: R223.2, U14.6
R5-8: R224.2, U14.7
R6-1: R265.2, U17.15
R6-2: R266.2, U17.1
R6-3: R267.2, U17.2
R6-4: R268.2, U17.3
R6-5: R269.2, U17.4
R6-6: R270.2, U17.5
R6-7: R271.2, U17.6
R6-8: R272.2, U17.7
R7-1: R313.2, U20.15
R7-2: R314.2, U20.1
R7-3: R315.2, U20.2
R7-4: R316.2, U20.3
R7-5: R317.2, U20.4
R7-6: R318.2, U20.5
R7-7: R319.2, U20.6
R7-8: R320.2, U20.7
R8-1: R361.2, U23.15
R8-2: R362.2, U23.1
R8-3: R363.2, U23.2
R8-4: R364.2, U23.3
R8-5: R365.2, U23.4
R8-6: R366.2, U23.5
R8-7: R367.2, U23.6
R8-8: R368.2, U23.7
Touch1: ESP1.33, SW1.1, SW1.2, TOUCH1.1
Touch2: ESP1.34, SW2.1, SW2.2, TOUCH2.1
Touch3: ESP1.35, SW3.1, SW3.2, TOUCH3.1
Touch4: ESP1.15, SW4.1, SW4.2, TOUCH4.1
Touch5: ESP1.13, SW5.1, SW5.2, TOUCH5.1
output_enable: ESP1.31, R410.2, U1.13, U2.13, U3.13, U4.13, U5.13, U6.13, U7.13, U8.13, U9.13, U10.13, U11.13, U12.13, U13.13, U14.13, U15.13, U16.13, U17.13, U18.13, U19.13, U20.13, U21.13, U22.13, U23.13, U24.13, U25.13
reset: ESP1.32, R413.1, U1.10, U2.10, U3.10, U4.10, U5.10, U6.10, U7.10, U8.10, U9.10, U10.10, U11.10, U12.10, U13.10, U14.10, U15.10, U16.10, U17.10, U18.10, U19.10, U20.10, U21.10, U22.10, U23.10, U24.10, U25.10
shifting_clock: ESP1.28, R412.2, U1.11, U2.11, U3.11, U4.11, U5.11, U6.11, U7.11, U8.11, U9.11, U10.11, U11.11, U12.11, U13.11, U14.11, U15.11, U16.11, U17.11, U18.11, U19.11, U20.11, U21.11, U22.11, U23.11, U24.11, U25.11
update_latch: ESP1.30, R411.2, U1.12, U2.12, U3.12, U4.12, U5.12, U6.12, U7.12, U8.12, U9.12, U10.12, U11.12, U12.12, U13.12, U14.12, U15.12, U16.12, U17.12, U18.12, U19.12, U20.12, U21.12, U22.12, U23.12, U24.12, U25.12

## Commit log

2021-09-12 Create project
2021-09-13 test
2021-09-13 Pin writing speed test
2021-09-28 Timer interrupt test
2021-09-28 Bit angle modulation test
2021-11-10 PCB update
2021-11-18 Alost finished PCB update
2021-11-21 Update fp-info-cache
2021-11-30 FINAL PCB update and some middle testing code update
2021-12-02 Rainbow, BAM, interrupt speed test
2021-12-08 Touch test
2021-12-10 PCB bug fix v1.1
2021-12-19 Basic 3d data shifting and multiplexing
